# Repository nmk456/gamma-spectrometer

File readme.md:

# Python Environment Setup

Tested on Python 3.13, should work on >=3.9

Windows:

```bat
python3 -m venv venv
venv\Scripts\activate.bat
pip install -r requirements.txt
```

Run sim:

```bat
cd sim

python sim_linear.py
```

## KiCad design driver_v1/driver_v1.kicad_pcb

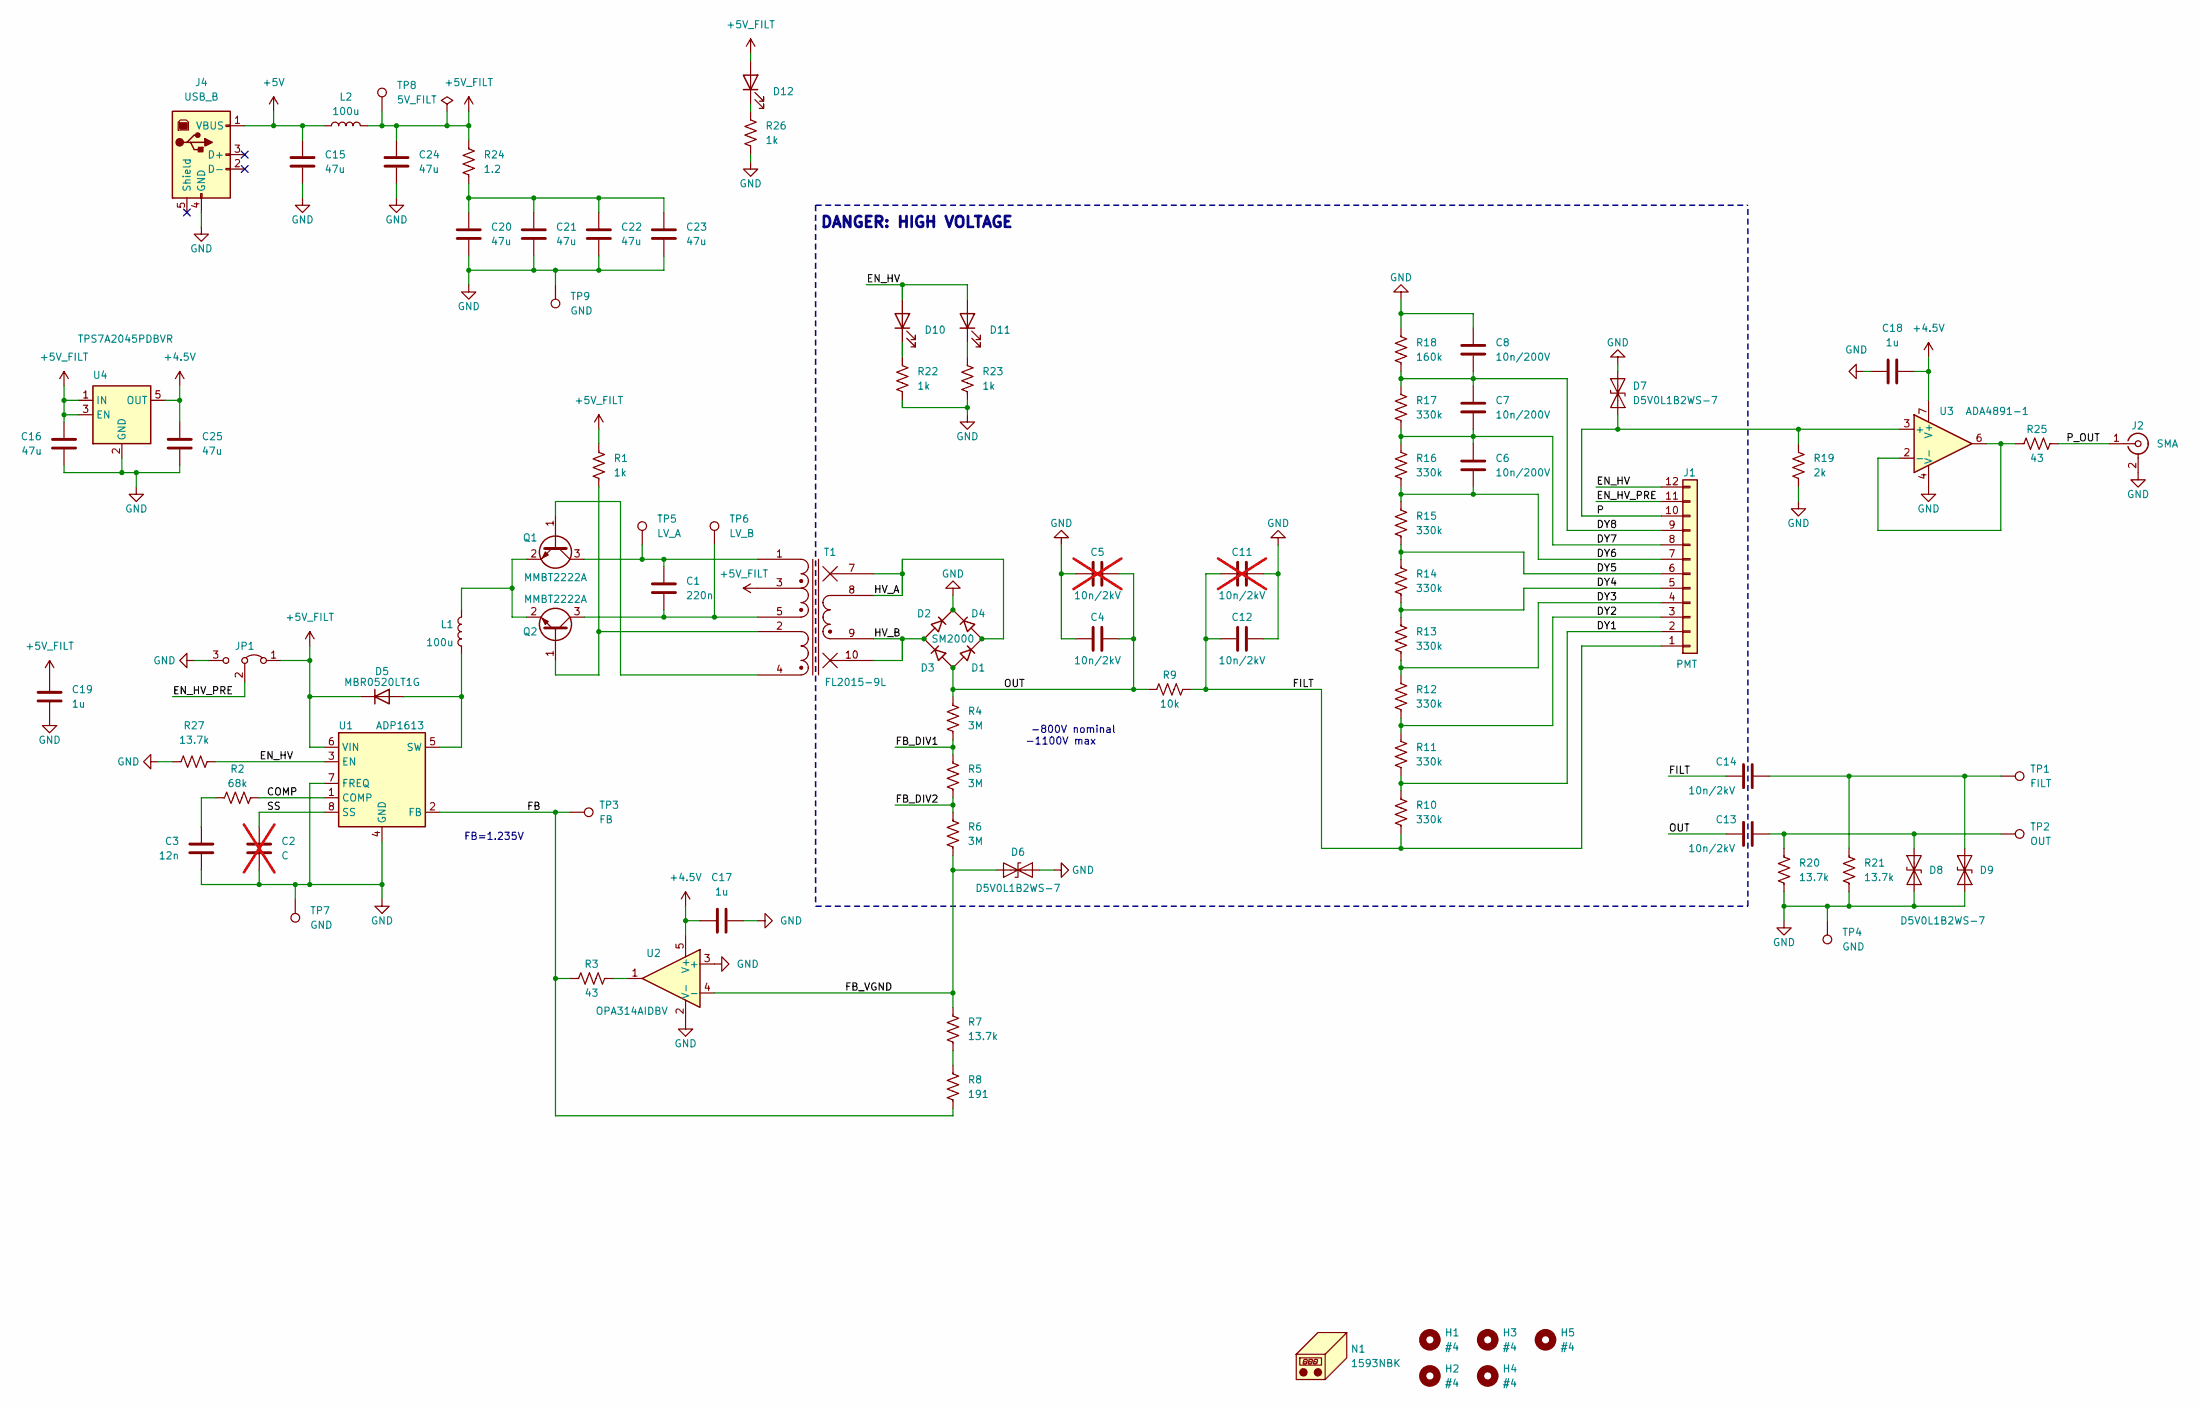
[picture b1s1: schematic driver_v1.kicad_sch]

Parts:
C1: 220n; C_0805_2012Metric_Pad1.18x1.45mm_HandSolder; DIGIKEY_PN 1276-7012-1-ND
C2: C; C_0603_1608Metric_Pad1.08x0.95mm_HandSolder; not fitted
C3: 12n; C_0603_1608Metric_Pad1.08x0.95mm_HandSolder; DIGIKEY_PN 399-C0603C123K4RACTUCT-ND
C4, C12, C13, C14: 10n/2kV; C_1812_4532Metric_Pad1.57x3.40mm_HandSolder; DIGIKEY_PN 4587-C1812X103K202TCT-ND
C5, C11: 10n/2kV; C_1812_4532Metric_Pad1.57x3.40mm_HandSolder; DIGIKEY_PN 4587-C1812X103K202TCT-ND; not fitted
C6, C7, C8: 10n/200V; C_0805_2012Metric_Pad1.18x1.45mm_HandSolder; DIGIKEY_PN 732-12169-1-ND
C15, C16, C20, C21, C22, C23, C24, C25: 47u; C_1210_3225Metric_Pad1.33x2.70mm_HandSolder; DIGIKEY_PN 587-5922-1-ND
C17, C18, C19: 1u; C_0603_1608Metric_Pad1.08x0.95mm_HandSolder; DIGIKEY_PN 1276-1946-1-ND
D1, D2, D3, D4: SM2000; D_MELF_Handsoldering; DIGIKEY_PN 4878-SM2000CT-ND
D5: MBR0520LT1G; D_SOD-123; DIGIKEY_PN MBR0520LT1GOSCT-ND
D6, D7, D8, D9: D5V0L1B2WS-7; D_SOD-323_HandSoldering; DIGIKEY_PN D5V0L1B2WS-7DICT-ND
D10, D11: LED; LED_D3.0mm_Horizontal_O3.81mm_Z2.0mm; DIGIKEY_PN 67-1058-ND
D12: LED; LED_D3.0mm_Horizontal_O3.81mm_Z2.0mm; DIGIKEY_PN 67-1073-ND
H1, H2, H3, H4, H5: #4; MountingHole_3.2mm_M3; DIGIKEY_PN SR6004-ND
J1: PMT; JST_XH_S12B-XH-A_1x12_P2.50mm_Horizontal; DIGIKEY_PN 455-2221-ND
J2: SMA; SMA_Molex_73251-2200_Horizontal; DIGIKEY_PN WM9352-ND
J4: USB_B; USB_B_OST_USB-B1HSxx_Horizontal; DIGIKEY_PN 102-3999-ND
JP1: Jumper_3_Bridged12; PinHeader_1x03_P2.54mm_Vertical
L1, L2: 100u; L_Taiyo-Yuden_NR-80xx_HandSoldering; DIGIKEY_PN 587-NRS8040T101MJGKCT-ND
N1: 1593NBK; DIGIKEY_PN HM963-ND
Q1, Q2: MMBT2222A; SOT-23_Handsoldering; DIGIKEY_PN MMBT2222A-FDICT-ND
R1, R22, R23, R26: 1k; R_0603_1608Metric_Pad0.98x0.95mm_HandSolder; DIGIKEY_PN P1.00KHCT-ND
R2: 68k; R_0603_1608Metric_Pad0.98x0.95mm_HandSolder; DIGIKEY_PN P68.0KHCT-ND
R3, R25: 43; R_0603_1608Metric_Pad0.98x0.95mm_HandSolder; DIGIKEY_PN P43.0HCT-ND
R4, R5, R6: 3M; R_1206_3216Metric_Pad1.30x1.75mm_HandSolder; DIGIKEY_PN 408-RGV3216P-3004-B-T1CT-ND
R7, R20, R21, R27: 13.7k; R_0603_1608Metric_Pad0.98x0.95mm_HandSolder; DIGIKEY_PN P13.7KDBCT-ND
R8: 191; R_0603_1608Metric_Pad0.98x0.95mm_HandSolder; DIGIKEY_PN P191DBCT-ND
R9: 10k; R_0805_2012Metric_Pad1.20x1.40mm_HandSolder; DIGIKEY_PN P10KACT-ND
R10, R11, R12, R13, R14, R15, R16, R17: 330k; R_0805_2012Metric_Pad1.20x1.40mm_HandSolder; DIGIKEY_PN YAG5980CT-ND
R18: 160k; R_0805_2012Metric_Pad1.20x1.40mm_HandSolder; DIGIKEY_PN 13-RT0805FRE07160KLCT-ND
R19: 2k; R_0603_1608Metric_Pad0.98x0.95mm_HandSolder; DIGIKEY_PN P2.00KHCT-ND
R24: 1.2; R_0603_1608Metric_Pad0.98x0.95mm_HandSolder; DIGIKEY_PN P1.3GCT-ND
T1: FL2015-9L; Coilcraft_FL2015
TP1: FILT; TestPoint_Keystone_5010-5014_Multipurpose; DIGIKEY_PN 36-5013-ND
TP2: OUT; TestPoint_Keystone_5010-5014_Multipurpose; DIGIKEY_PN 36-5013-ND
TP3: FB; TestPoint_Keystone_5010-5014_Multipurpose; DIGIKEY_PN 36-5012-ND
TP4, TP7, TP9: GND; TestPoint_Keystone_5010-5014_Multipurpose; DIGIKEY_PN 36-5011-ND
TP5: LV_A; TestPoint_Keystone_5010-5014_Multipurpose; DIGIKEY_PN 36-5012-ND
TP6: LV_B; TestPoint_Keystone_5010-5014_Multipurpose; DIGIKEY_PN 36-5012-ND
TP8: 5V_FILT; TestPoint_Keystone_5010-5014_Multipurpose; DIGIKEY_PN 36-5010-ND
U1: ADP1613; MSOP-8_3x3mm_P0.65mm; DIGIKEY_PN 505-ADP1613ARMZ-R7CT-ND
U2: OPA314AIDBV; SOT-23-5_HandSoldering; DIGIKEY_PN 296-36699-1-ND
U3: ADA4891-1; SOIC-8_3.9x4.9mm_P1.27mm; DIGIKEY_PN 505-ADA4891-1ARZ-R7CT-ND
U4: TPS7A2045PDBVR; SOT-23-5; DIGIKEY_PN 296-TPS7A2045PDBVRCT-ND

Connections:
+4.5V: C17.1, C18.1, C25.1, U2.5 (V+), U3.7 (V+), U4.5 (OUT)
+5V: C15.1, J4.1 (VBUS), L2.1
+5V_FILT: C16.1, C19.1, C24.1, D5.1 (K), D12.2 (A), JP1.1 (A), L2.2, R1.1, R24.1, T1.3 (IN_B), TP8.1, U1.6 (VIN), U4.1 (IN), U4.3 (EN)
/COMP: R2.2, U1.1 (COMP)
/DY1: J1.2, R10.1, R11.2
/DY2: J1.3, R11.1, R12.2
/DY3: J1.4, R12.1, R13.2
/DY4: J1.5, R13.1, R14.2
/DY5: J1.6, R14.1, R15.2
/DY6: C6.2, J1.7, R15.1, R16.2
/DY7: C6.1, C7.2, J1.8, R16.1, R17.2
/DY8: C7.1, C8.2, J1.9, R17.1, R18.2
/EN_HV: D10.2 (A), D11.2 (A), J1.12, R27.1, U1.3 (EN)
/EN_HV_PRE: J1.11, JP1.2 (C)
/FB: R3.1, R8.1, TP3.1, U1.2 (FB)
/FB_DIV1: R4.2, R5.1
/FB_DIV2: R5.2, R6.1
/FB_VGND: D6.1 (A1), R6.2, R7.2, U2.4 (-)
/FILT: C11.1, C12.1, C14.2, J1.1, R9.2, R10.2
/HV_A: D1.1 (K), D4.2 (A), T1.7 (NC), T1.8 (OUT_A)
/HV_B: D2.2 (A), D3.1 (K), T1.9 (OUT_B), T1.10 (NC)
/OUT: C4.2, C5.2, C13.2, D1.2 (A), D3.2 (A), R4.1, R9.1
/P: D7.1 (A1), J1.10, R19.1, U3.3 (+)
/P_OUT: J2.1 (In), R25.2
/SS: C2.1, U1.8 (SS)
GND: C2.2, C3.2, C4.1, C5.1, C8.1, C11.2, C12.2, C15.2, C16.2, C17.2, C18.2, C19.2, C20.2, C21.2, C22.2, C23.2, C24.2, C25.2, D2.1 (K), D4.1 (K), D6.2 (A2), D7.2 (A2), D8.1 (A1), D9.1 (A1), J2.2 (Ext), J4.4 (GND), JP1.3 (B), R18.1, R19.2, R20.1, R21.1, R22.2, R23.2, R26.2, R27.2, TP4.1, TP7.1, TP9.1, U1.4 (GND), U1.7 (FREQ), U2.2 (V-), U2.3 (+), U3.4 (V-), U4.2 (GND)
unnamed: C3.1, R2.1
unnamed: C20.1, C21.1, C22.1, C23.1, R24.2
unnamed: D5.2 (A), L1.1, U1.5 (SW)
unnamed: C13.1, D8.2 (A2), R20.2, TP2.1
unnamed: C14.1, D9.2 (A2), R21.2, TP1.1
unnamed: D10.1 (K), R22.1
unnamed: D11.1 (K), R23.1
unnamed: D12.1 (K), R26.1
unnamed: Q1.1 (B), T1.4 (FB_B)
unnamed: C1.1, Q1.3 (C), T1.1 (IN_A), TP5.1
unnamed: L1.2, Q1.2 (E), Q2.2 (E)
unnamed: Q2.1 (B), R1.2, T1.2 (FB_A)
unnamed: C1.2, Q2.3 (C), T1.5 (IN_C), TP6.1
unnamed: R3.2, U2.1
unnamed: R7.1, R8.2
unnamed: R25.1, U3.2 (-), U3.6

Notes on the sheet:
FB=1.235V
-800V nominal -1100V max
DANGER: HIGH VOLTAGE

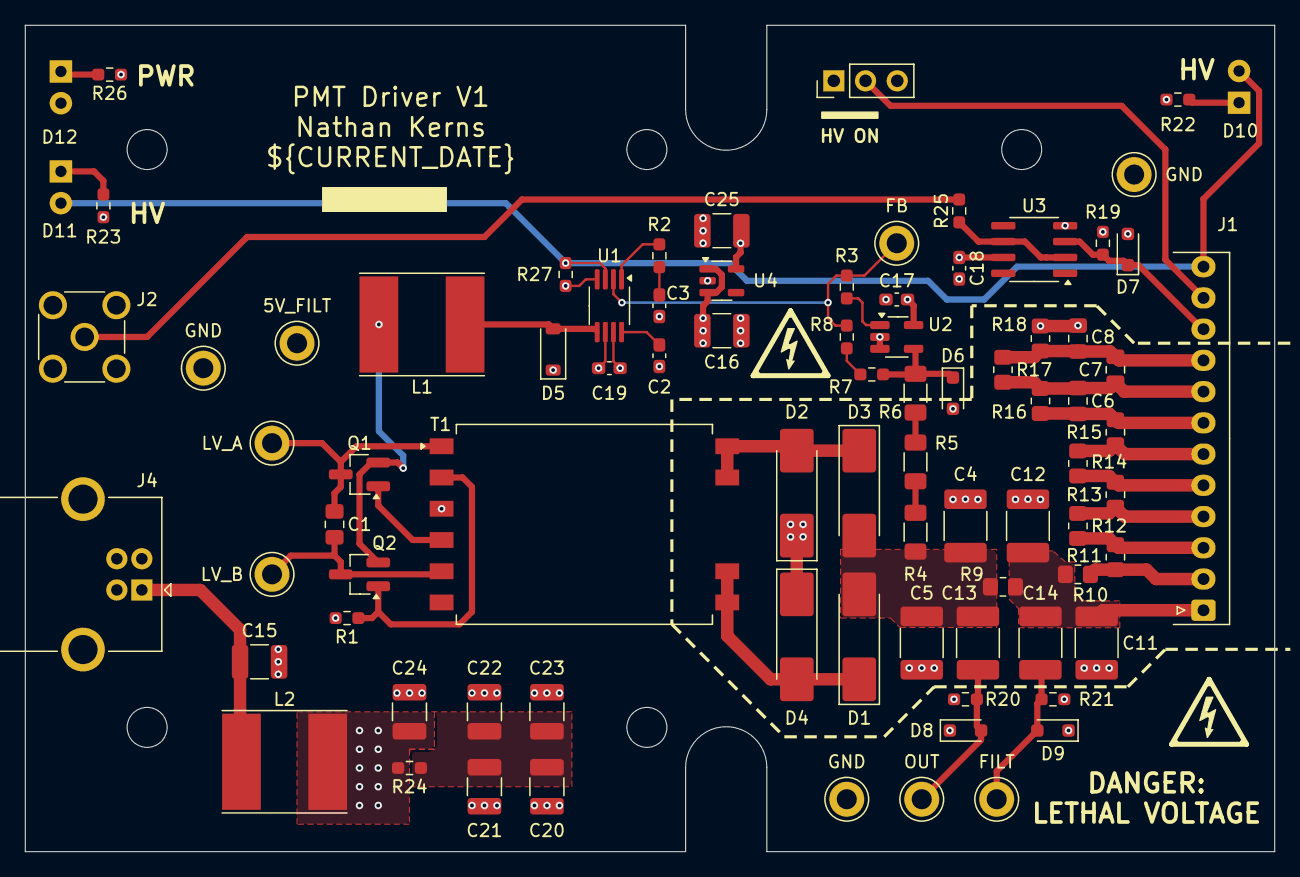
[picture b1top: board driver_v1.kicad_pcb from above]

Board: 4 copper layers, 100.0 x 66.1 mm, 89 parts (0 on the bottom side), 42 nets.

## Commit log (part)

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2025-02-15 Sims
2025-02-15 PCBs
2025-02-15 DC current symbol
2025-02-15 Swap LEDs, update 3D models
2025-02-15 Increase LED cutout radius, add back panel
2025-02-15 Move front panel text
2025-02-15 Add jlc jobset
2025-02-16 Update jobset and gitignore
2025-02-16 Add script to run all jobsets
2025-02-16 Include screws in BOM, add serial number location
2025-03-01 Test github actions
2025-03-01 Fix permissions
2025-03-01 Run as root
2025-03-01 Fix artifact names
2025-03-01 Test release
2025-03-01 Fix violations for 9.0
2025-03-01 Fix symbol table
2025-03-01 Ignore ERC violations
2025-03-01 Add fillets to back panel cutout
2025-06-30 Add BOM, fix datasheet
2025-06-30 Rename sim file
2025-08-11 Start automating sims
2025-08-17 Add enable switch, changed mosfet
2025-08-18 Use better op amp model, parallelize sim
2025-08-18 Python env setup
